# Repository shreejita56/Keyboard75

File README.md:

# Keyboard75

SO I made a custom 75 % layout Mechanical keyboard which has a rotor encoder at the top for brightness controlee as well . It is based on rp2040 chip  . SO I had to design the MCU circuit by myself as well . The PCB was designed on kicad and CAD was done on Fusion . firmware was written in VS-Code. It has a very compact design. The Keyboard also includes per switch LED and diodes to prevent ghosting. It connects to the PC via USB-C input .

## Features
 - Based on Rp2040 chip
 - had compact 75% keyboard layout
 - Per Switch LED and diode for ghosting prevention
 - USB-C Type for Connection
 - Uplifted CAD Design for comfortable typing

##  BOM

| Comment | Footprint | Quantity | Total Price ($) | Link |
|---|---|---:|---:|---|
| 33pF | 0603 | 4 | 0.0236 | https://jlcpcb.com/partdetail/2015-CL10C330JB8NNNC/C1663 |
| 0.1uF | 0603 | 10 | 0.124 | https://jlcpcb.com/partdetail/YAGEO-CC0603KRX7R9BB104/C14663 |
| 100nF | 0603 | 10 | 0.124 | https://jlcpcb.com/partdetail/YAGEO-CC0603KRX7R9BB104/C14663 |
| 10uF | 0603 | 4 | 0.1276 | https://jlcpcb.com/partdetail/20411-CL10A106KP8NNNC/C19702 |
| 1uF | 0603 | 4 | 0.0684 | https://jlcpcb.com/partdetail/16531-CL10A105KB8NNNC/C15849 |
| USB_C_Receptacle_USB2.0_16P | USB_C_Receptacle_G-Switch_GT-USB-7010ASV | 2 | 0.0988 | https://jlcpcb.com/partdetail/DEALON-USB_TYPE_C006/C2927026 |
| 5.1K | 0603 | 4 | 0.0076 | https://jlcpcb.com/partdetail/23913-0603WAF5101T5E/C23186 |
| 1K | 0603 | 4 | 0.0132 | https://jlcpcb.com/partdetail/21904-0603WAF1001T5E/C21190 |
| 27ohm | 0603 | 20 | 0.022 | https://jlcpcb.com/partdetail/23790019-RCA0327RJLF/C22356575 |
| 10K | 0603 | 4 | 0.0108 | https://jlcpcb.com/partdetail/26547-0603WAF1002T5E/C25804 |
| RP2040 | QFN-56-1EP_7x7mm_P0.4mm_EP3.2x3.2mm | 2 | 1.979 | https://jlcpcb.com/partdetail/RaspberryPi-RP2040/C2040 |
| 12MHz | Crystal_SMD_3225-4Pin_3.2x2.5mm | 5 | 2.14 | https://jlcpcb.com/partdetail/KDSDaishinku-DSX321G12MHz/C93234 |
| PCB + 3D Prints Cost | — | 1 | 30.80 | https://jlcpcb.com |
| PCBA Cost | — | 1 | 27.88 | https://jlcpcb.com |
| PCB Shipping | — | 1 | 14.03 | https://jlcpcb.com |
| Hot-swap | — | 90 | 6.75 | https://meckeys.com/shop/accessories/keyboard-accessories/key-switches/kailh-hot-swap-socket/?attribute_pa_variations=white |
| Mechanical Switch | — | 90 | 21.10 | https://meckeys.com/shop/accessories/keyboard-accessories/key-switches/akko-v3-pro-cream-black-switch/ |
| KEY-CAPS | — | 1 | 11.50 | https://meckeys.com/shop/accessories/keyboard-accessories/keycaps/side-engraved-keycap-set/?attribute_pa_pick-your-style=blackberry-side-printed |
| 0.1uF Capacitor | 0603 | 90 | 3.60 | https://sharvielectronics.com/product/0-1uf-16v-capacitor-0603-smd-package/ |
| 1N4007 Diodes | SOD-123FL | 90 | 2.60 | https://sharvielectronics.com/product/a7-1n4007-100v-1a-silicon-rectifier-diode-sod-123fl-smd-package/ |
| SK6812MINI-E | — | 90 | 8.10 | https://www.etstore.in/products/e9974?variant=48993209319675 |
| Components Shipping | — | 1 | 3.30 | https://www.etstore.in/ |
| **TOTAL** | — | — | **$132.67** | — |

### Schematic<br><br>

###  PCB Design<br><br>

### 3D Render <br><br>

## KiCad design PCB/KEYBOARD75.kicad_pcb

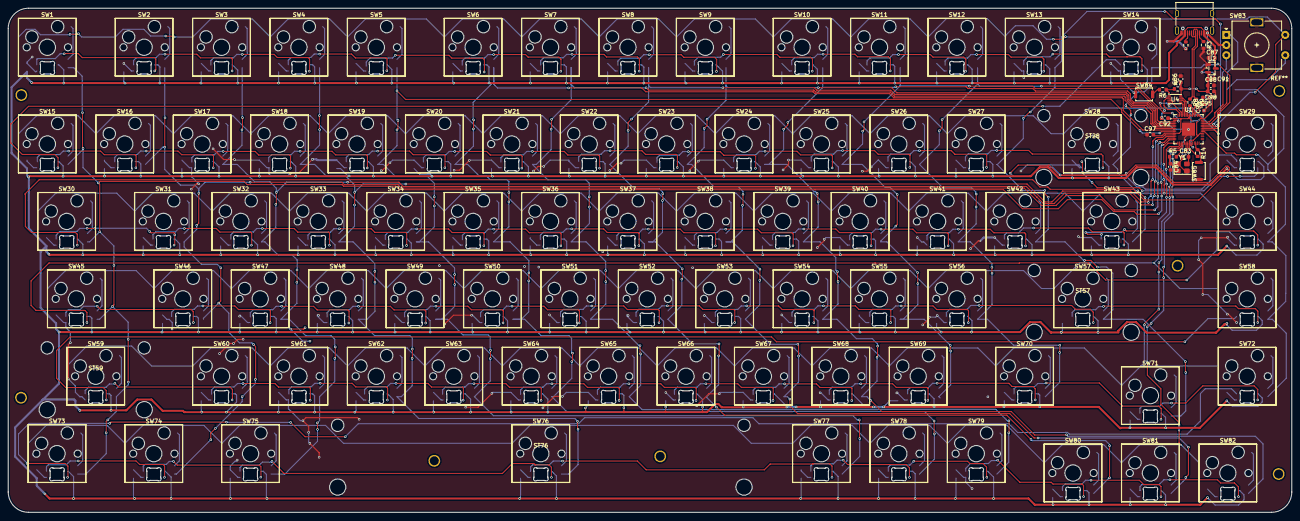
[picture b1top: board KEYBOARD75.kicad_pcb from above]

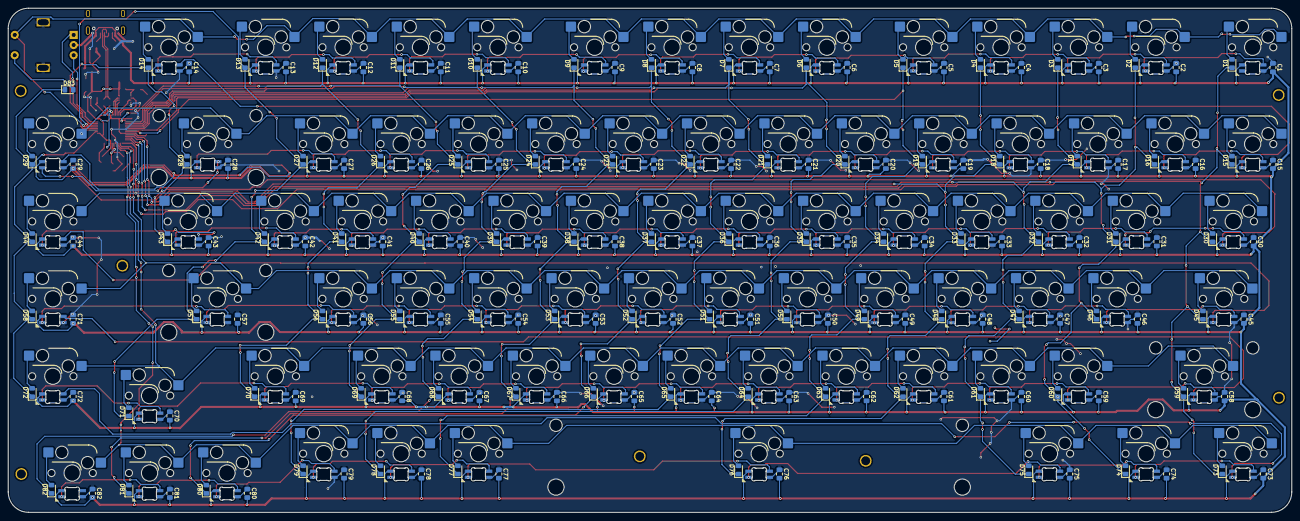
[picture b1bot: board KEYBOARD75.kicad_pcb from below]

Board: 2 copper layers, 315.9 x 124.1 mm, 360 parts (165 on the bottom side), 208 nets.

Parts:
C1, C2, C3, C4, C5, C6, C7, C8, C9, C10, C11, C12, C13, C14, C15, C16, C17, C18, C19, C20, C21, C22, C23, C24, C25, C26, C27, C28, C29, C30, C31, C32, C33, C34, C35, C36, C37, C38, C39, C40, C41, C42, C43, C44, C45, C46, C47, C48, C49, C50, C51, C52, C53, C54, C55, C56, C57, C58, C59, C60, C61, C62, C63, C64, C65, C66, C67, C68, C69, C70, C71, C72, C73, C74, C75, C76, C77, C78, C79, C80, C81, C82: 0.1 uf; C_0805_2012Metric_Pad1.18x1.45mm_HandSolder
C83, C84: 33pF; C_0603_1608Metric
C86, C88, C92: 0.1uF; C_0603_1608Metric
C87, C91: 10uF; C_0603_1608Metric
C94: 1uF; C_0603_1608Metric
C95, C97: 100 nf; C_0603_1608Metric
C98: 1uf; C_0603_1608Metric
D1, D2, D3, D4, D5, D6, D7, D8, D9, D10, D11, D12, D13, D14, D15, D16, D17, D18, D19, D20, D21, D22, D23, D24, D25, D26, D27, D28, D29, D30, D31, D32, D33, D34, D35, D36, D37, D38, D39, D40, D41, D42, D43, D44, D45, D46, D47, D48, D49, D50, D51, D52, D53, D54, D55, D56, D57, D58, D59, D60, D61, D62, D63, D64, D65, D66, D67, D68, D69, D70, D71, D72, D73, D74, D75, D76, D77, D78, D79, D80, D81, D82, D83: D; D_0805_2012Metric_Pad1.15x1.40mm_HandSolder
J1: USB_C_Receptacle_USB2.0_16P; USB_C_Receptacle_G-Switch_GT-USB-7010ASV
LED1: C; MX_SK6812MINI-E
LED2, LED3, LED4, LED5, LED6, LED7, LED8, LED9, LED10, LED11, LED12, LED13, LED14, LED15, LED16, LED17, LED18, LED19, LED20, LED21, LED22, LED23, LED24, LED25, LED26, LED27, LED28, LED29, LED30, LED31, LED32, LED33, LED34, LED35, LED36, LED37, LED38, LED39, LED40, LED41, LED42, LED43, LED44, LED45, LED46, LED47, LED48, LED49, LED50, LED51, LED52, LED53, LED54, LED55, LED56, LED57, LED58, LED59, LED60, LED61, LED62, LED63, LED64, LED65, LED66, LED67, LED68, LED69, LED70, LED71, LED72, LED73, LED74, LED75, LED76, LED77, LED78, LED79, LED80, LED81, LED82: MX_SK6812MINI-E
R3, R4: 5.1K; R_0603_1608Metric
R5, R6: 1K; R_0603_1608Metric
R7, R14: 10K; R_0603_1608Metric
R8, R9: 27 ohn; R_0603_1608Metric
ST28, ST57, ST59: MountingHole; Stabilizer_Cherry_MX_2.00u
ST76: MountingHole; Stabilizer_Cherry_MX_6.25u
SW1: ESC; SW_Hotswap_Kailh_MX_1.00u
SW2: F1; SW_Hotswap_Kailh_MX_1.00u
SW3: F2; SW_Hotswap_Kailh_MX_1.00u
SW4: F3; SW_Hotswap_Kailh_MX_1.00u
SW5: F4; SW_Hotswap_Kailh_MX_1.00u
SW6: F5; SW_Hotswap_Kailh_MX_1.00u
SW7: F6; SW_Hotswap_Kailh_MX_1.00u
SW8: F7; SW_Hotswap_Kailh_MX_1.00u
SW9: F8; SW_Hotswap_Kailh_MX_1.00u
SW10: F9; SW_Hotswap_Kailh_MX_1.00u
SW11: F10; SW_Hotswap_Kailh_MX_1.00u
SW12: F11; SW_Hotswap_Kailh_MX_1.00u
SW13: F12; SW_Hotswap_Kailh_MX_1.00u
SW14: Delete; SW_Hotswap_Kailh_MX_1.00u
SW15: `; SW_Hotswap_Kailh_MX_1.00u
SW16: 1; SW_Hotswap_Kailh_MX_1.00u
SW17: 2; SW_Hotswap_Kailh_MX_1.00u
SW18: 3; SW_Hotswap_Kailh_MX_1.00u
SW19: 4; SW_Hotswap_Kailh_MX_1.00u
SW20: 5; SW_Hotswap_Kailh_MX_1.00u
SW21: 6; SW_Hotswap_Kailh_MX_1.00u
SW22: 7; SW_Hotswap_Kailh_MX_1.00u
SW23: 8; SW_Hotswap_Kailh_MX_1.00u
SW24: 9; SW_Hotswap_Kailh_MX_1.00u
SW25: 0; SW_Hotswap_Kailh_MX_1.00u
SW26: -; SW_Hotswap_Kailh_MX_1.00u
SW27: +; SW_Hotswap_Kailh_MX_1.00u
SW28: Backspace; SW_Hotswap_Kailh_MX_1.00u
SW29: Home; SW_Hotswap_Kailh_MX_1.00u
SW30: Tab; SW_Hotswap_Kailh_MX_1.00u
SW31: Q; SW_Hotswap_Kailh_MX_1.00u
SW32: W; SW_Hotswap_Kailh_MX_1.00u
SW33: E; SW_Hotswap_Kailh_MX_1.00u
SW34: R; SW_Hotswap_Kailh_MX_1.00u
SW35: T; SW_Hotswap_Kailh_MX_1.00u
SW36: Y; SW_Hotswap_Kailh_MX_1.00u
SW37: U; SW_Hotswap_Kailh_MX_1.00u
SW38: I; SW_Hotswap_Kailh_MX_1.00u
SW39: O; SW_Hotswap_Kailh_MX_1.00u
SW40: P; SW_Hotswap_Kailh_MX_1.00u
SW41: [; SW_Hotswap_Kailh_MX_1.00u
SW42: ]; SW_Hotswap_Kailh_MX_1.00u
SW43: \; SW_Hotswap_Kailh_MX_1.00u
SW44: Pg Up; SW_Hotswap_Kailh_MX_1.00u
SW45: Caps Lock; SW_Hotswap_Kailh_MX_1.00u
SW46: A; SW_Hotswap_Kailh_MX_1.00u
SW47: S; SW_Hotswap_Kailh_MX_1.00u
SW48: D; SW_Hotswap_Kailh_MX_1.00u
SW49: F; SW_Hotswap_Kailh_MX_1.00u
SW50: G; SW_Hotswap_Kailh_MX_1.00u
SW51: H; SW_Hotswap_Kailh_MX_1.00u
SW52: J; SW_Hotswap_Kailh_MX_1.00u
SW53: K; SW_Hotswap_Kailh_MX_1.00u
SW54: L; SW_Hotswap_Kailh_MX_1.00u
SW55: ;; SW_Hotswap_Kailh_MX_1.00u
SW56: "; SW_Hotswap_Kailh_MX_1.00u
SW57: Enter; SW_Hotswap_Kailh_MX_1.00u
SW58: Pg Dn; SW_Hotswap_Kailh_MX_1.00u
SW59: L Shift; SW_Hotswap_Kailh_MX_1.00u
SW60: Z; SW_Hotswap_Kailh_MX_1.00u
SW61: X; SW_Hotswap_Kailh_MX_1.00u
SW62: C; SW_Hotswap_Kailh_MX_1.00u
SW63: V; SW_Hotswap_Kailh_MX_1.00u
SW64: B; SW_Hotswap_Kailh_MX_1.00u
SW65: N; SW_Hotswap_Kailh_MX_1.00u
SW66: M; SW_Hotswap_Kailh_MX_1.00u
SW67: ,; SW_Hotswap_Kailh_MX_1.00u
SW68: .; SW_Hotswap_Kailh_MX_1.00u
SW69: /; SW_Hotswap_Kailh_MX_1.00u
SW70: R Shift; SW_Hotswap_Kailh_MX_1.00u
SW71: Up Arrow; SW_Hotswap_Kailh_MX_1.00u
SW72: End; SW_Hotswap_Kailh_MX_1.00u
SW73: L Ctrl; SW_Hotswap_Kailh_MX_1.00u
SW74: Win; SW_Hotswap_Kailh_MX_1.00u
SW75, SW77: Alt; SW_Hotswap_Kailh_MX_1.00u
SW76: Space; SW_Hotswap_Kailh_MX_1.00u
SW78: Fn; SW_Hotswap_Kailh_MX_1.00u
SW79: R Ctrl; SW_Hotswap_Kailh_MX_1.00u
SW80: Left Arrow; SW_Hotswap_Kailh_MX_1.00u
SW81: Down Arrow; SW_Hotswap_Kailh_MX_1.00u
SW82: Right Arrow; SW_Hotswap_Kailh_MX_1.00u
SW83: RotaryEncoder_Switch_MP; RotaryEncoder_Alps_EC11E-Switch_Vertical_H20mm
SW84, SW85: SW_Push; SW_Push_SPST_NO_Alps_SKRK
U1: RP2040; QFN-56-1EP_7x7mm_P0.4mm_EP3.2x3.2mm
U2: MCP1700x-330xxTT; SOT-23
U4: W25Q16JVUXIQ TR; Winbond_USON-8-1EP_3x2mm_P0.5mm_EP0.2x1.6mm
Y1: 12 MHz; Crystal_SMD_3225-4Pin_3.2x2.5mm

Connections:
+3.3V: C86.1, C88.1, C91.1, C92.1, C97.2, C98.2, R7.2, R14.2, U1.1 (IOVDD), U1.10 (IOVDD), U1.22 (IOVDD), U1.33 (IOVDD), U1.42 (IOVDD), U1.43 (ADC_AVDD), U1.44 (VREG_IN), U1.48 (USB_VDD), U1.49 (IOVDD), U2.2 (VO), U4.8 (VCC)
+5V: C1.2, C2.2, C3.2, C4.2, C5.2, C6.2, C7.2, C8.2, C9.2, C10.2, C11.2, C12.2, C13.2, C14.2, C15.2, C16.2, C17.2, C18.2, C19.2, C20.2, C21.2, C22.2, C23.2, C24.2, C25.2, C26.2, C27.2, C28.2, C29.2, C30.2, C31.2, C32.2, C33.2, C34.2, C35.2, C36.2, C37.2, C38.2, C39.2, C40.2, C41.2, C42.2, C43.2, C44.2, C45.2, C46.2, C47.2, C48.2, C49.2, C50.2, C51.2, C52.2, C53.2, C54.2, C55.2, C56.2, C57.2, C58.2, C59.2, C60.2, C61.2, C62.2, C63.2, C64.2, C65.2, C66.2, C67.2, C68.2, C69.2, C70.2, C71.2, C72.2, C73.2, C74.2, C75.2, C76.2, C77.2, C78.2, C79.2, C80.2, C81.2, C82.2, C87.1, J1.A4 (VBUS), J1.A9 (VBUS), J1.B4 (VBUS), J1.B9 (VBUS), LED1.4 (VDD), LED2.4 (VDD), LED3.4 (VDD), LED4.4 (VDD), LED5.4 (VDD), LED6.4 (VDD), LED7.4 (VDD), LED8.4 (VDD), LED9.4 (VDD), LED10.4 (VDD), LED11.4 (VDD), LED12.4 (VDD), LED13.4 (VDD), LED14.4 (VDD), LED15.4 (VDD), LED16.4 (VDD), LED17.4 (VDD), LED18.4 (VDD), LED19.4 (VDD), LED20.4 (VDD), LED21.4 (VDD), LED22.4 (VDD), LED23.4 (VDD), LED24.4 (VDD), LED25.4 (VDD), LED26.4 (VDD), LED27.4 (VDD), LED28.4 (VDD), LED29.4 (VDD), LED30.4 (VDD), LED31.4 (VDD), LED32.4 (VDD), LED33.4 (VDD), LED34.4 (VDD), LED35.4 (VDD), LED36.4 (VDD), LED37.4 (VDD), LED38.4 (VDD), LED39.4 (VDD), LED40.4 (VDD), LED41.4 (VDD), LED42.4 (VDD), LED43.4 (VDD), LED44.4 (VDD), LED45.4 (VDD), LED46.4 (VDD), LED47.4 (VDD), LED48.4 (VDD), LED49.4 (VDD), LED50.4 (VDD), LED51.4 (VDD), LED52.4 (VDD), LED53.4 (VDD), LED54.4 (VDD), LED55.4 (VDD), LED56.4 (VDD), LED57.4 (VDD), LED58.4 (VDD), LED59.4 (VDD), LED60.4 (VDD), LED61.4 (VDD), LED62.4 (VDD), LED63.4 (VDD), LED64.4 (VDD), LED65.4 (VDD), LED66.4 (VDD), LED67.4 (VDD), LED68.4 (VDD), LED69.4 (VDD), LED70.4 (VDD), LED71.4 (VDD), LED72.4 (VDD), LED73.4 (VDD), LED74.4 (VDD), LED75.4 (VDD), LED76.4 (VDD), LED77.4 (VDD), LED78.4 (VDD), LED79.4 (VDD), LED80.4 (VDD), LED81.4 (VDD), LED82.4 (VDD), U2.3 (VI)
C1: D1.1 (K), D15.1 (K), D30.1 (K), D45.1 (K), D59.1 (K), D73.1 (K), U1.14 (GPIO11)
C2: D2.1 (K), D16.1 (K), D31.1 (K), D46.1 (K), D60.1 (K), D74.1 (K), U1.13 (GPIO10)
C3: D3.1 (K), D17.1 (K), D32.1 (K), D47.1 (K), D61.1 (K), D75.1 (K), U1.12 (GPIO9)
C4: D4.1 (K), D18.1 (K), D33.1 (K), D48.1 (K), D62.1 (K), D76.1 (K), U1.11 (GPIO8)
C5: D5.1 (K), D19.1 (K), D34.1 (K), D49.1 (K), D63.1 (K), D77.1 (K), U1.9 (GPIO7)
C6: D6.1 (K), D20.1 (K), D35.1 (K), D50.1 (K), D64.1 (K), D78.1 (K), U1.8 (GPIO6)
C7: D7.1 (K), D21.1 (K), D36.1 (K), D51.1 (K), D65.1 (K), D79.1 (K), U1.7 (GPIO5)
C8: D8.1 (K), D22.1 (K), D37.1 (K), D52.1 (K), D66.1 (K), D80.1 (K), U1.6 (GPIO4)
C9: D9.1 (K), D23.1 (K), D38.1 (K), D53.1 (K), D67.1 (K), D81.1 (K), U1.5 (GPIO3)
C10: D10.1 (K), D24.1 (K), D39.1 (K), D54.1 (K), D68.1 (K), D82.1 (K), U1.4 (GPIO2)
C11: D11.1 (K), D25.1 (K), D40.1 (K), D55.1 (K), D69.1 (K), U1.3 (GPIO1)
C12: D12.1 (K), D26.1 (K), D41.1 (K), D56.1 (K), D70.1 (K), U1.2 (GPIO0)
C13: D13.1 (K), D27.1 (K), D42.1 (K), D57.1 (K), D71.1 (K), U1.38 (GPIO26_ADC0)
C14: D14.1 (K), D28.1 (K), D43.1 (K), U1.36 (GPIO24)
C15: D29.1 (K), D44.1 (K), D58.1 (K), D72.1 (K), D83.1 (K), U1.34 (GPIO22)
E-A: SW83.A, U1.39 (GPIO27_ADC1)
E-B: SW83.B, U1.40 (GPIO28_ADC2)
E-SW1: D83.2 (A), SW83.S1
E-SW2: SW1.1, SW2.1, SW3.1, SW4.1, SW5.1, SW6.1, SW7.1, SW8.1, SW9.1, SW10.1, SW11.1, SW12.1, SW13.1, SW14.1, SW83.S2, U1.37 (GPIO25)
GND: C1.1, C2.1, C3.1, C4.1, C5.1, C6.1, C7.1, C8.1, C9.1, C10.1, C11.1, C12.1, C13.1, C14.1, C15.1, C16.1, C17.1, C18.1, C19.1, C20.1, C21.1, C22.1, C23.1, C24.1, C25.1, C26.1, C27.1, C28.1, C29.1, C30.1, C31.1, C32.1, C33.1, C34.1, C35.1, C36.1, C37.1, C38.1, C39.1, C40.1, C41.1, C42.1, C43.1, C44.1, C45.1, C46.1, C47.1, C48.1, C49.1, C50.1, C51.1, C52.1, C53.1, C54.1, C55.1, C56.1, C57.1, C58.1, C59.1, C60.1, C61.1, C62.1, C63.1, C64.1, C65.1, C66.1, C67.1, C68.1, C69.1, C70.1, C71.1, C72.1, C73.1, C74.1, C75.1, C76.1, C77.1, C78.1, C79.1, C80.1, C81.1, C82.1, C83.1, C84.1, C86.2, C87.2, C88.2, C91.2, C92.2, C94.1, C95.1, C97.1, C98.1, J1.A1 (GND), J1.A12 (GND), J1.B1 (GND), J1.B12 (GND), LED1.2 (VSS), LED2.2 (VSS), LED3.2 (VSS), LED4.2 (VSS), LED5.2 (VSS), LED6.2 (VSS), LED7.2 (VSS), LED8.2 (VSS), LED9.2 (VSS), LED10.2 (VSS), LED11.2 (VSS), LED12.2 (VSS), LED13.2 (VSS), LED14.2 (VSS), LED15.2 (VSS), LED16.2 (VSS), LED17.2 (VSS), LED18.2 (VSS), LED19.2 (VSS), LED20.2 (VSS), LED21.2 (VSS), LED22.2 (VSS), LED23.2 (VSS), LED24.2 (VSS), LED25.2 (VSS), LED26.2 (VSS), LED27.2 (VSS), LED28.2 (VSS), LED29.2 (VSS), LED30.2 (VSS), LED31.2 (VSS), LED32.2 (VSS), LED33.2 (VSS), LED34.2 (VSS), LED35.2 (VSS), LED36.2 (VSS), LED37.2 (VSS), LED38.2 (VSS), LED39.2 (VSS), LED40.2 (VSS), LED41.2 (VSS), LED42.2 (VSS), LED43.2 (VSS), LED44.2 (VSS), LED45.2 (VSS), LED46.2 (VSS), LED47.2 (VSS), LED48.2 (VSS), LED49.2 (VSS), LED50.2 (VSS), LED51.2 (VSS), LED52.2 (VSS), LED53.2 (VSS), LED54.2 (VSS), LED55.2 (VSS), LED56.2 (VSS), LED57.2 (VSS), LED58.2 (VSS), LED59.2 (VSS), LED60.2 (VSS), LED61.2 (VSS), LED62.2 (VSS), LED63.2 (VSS), LED64.2 (VSS), LED65.2 (VSS), LED66.2 (VSS), LED67.2 (VSS), LED68.2 (VSS), LED69.2 (VSS), LED70.2 (VSS), LED71.2 (VSS), LED72.2 (VSS), LED73.2 (VSS), LED74.2 (VSS), LED75.2 (VSS), LED76.2 (VSS), LED77.2 (VSS), LED78.2 (VSS), LED79.2 (VSS), LED80.2 (VSS), LED81.2 (VSS), LED82.2 (VSS), R3.2, R4.2, SW83.C, SW83.MP, SW84.1, SW85.1, U1.19 (TESTEN), U1.57 (GND), U2.1 (GND), U4.4 (GND), Y1.2, Y1.4
unnamed: C84.2, R5.1, Y1.1
unnamed: D1.2 (A), SW1.2
unnamed: D2.2 (A), SW2.2
unnamed: D3.2 (A), SW3.2
unnamed: D4.2 (A), SW4.2
unnamed: D5.2 (A), SW5.2
unnamed: D6.2 (A), SW6.2
unnamed: D7.2 (A), SW7.2
unnamed: D8.2 (A), SW8.2
unnamed: D9.2 (A), SW9.2
unnamed: D10.2 (A), SW10.2
unnamed: D11.2 (A), SW11.2
unnamed: D12.2 (A), SW12.2
unnamed: D13.2 (A), SW13.2
unnamed: D14.2 (A), SW14.2
unnamed: D15.2 (A), SW15.2
unnamed: D16.2 (A), SW16.2
unnamed: D17.2 (A), SW17.2
unnamed: D18.2 (A), SW18.2
unnamed: D19.2 (A), SW19.2
unnamed: D20.2 (A), SW20.2
unnamed: D21.2 (A), SW21.2
unnamed: D22.2 (A), SW22.2
unnamed: D23.2 (A), SW23.2
unnamed: D24.2 (A), SW24.2
unnamed: D25.2 (A), SW25.2
unnamed: D26.2 (A), SW26.2
unnamed: D27.2 (A), SW27.2
unnamed: D28.2 (A), SW28.2
unnamed: D29.2 (A), SW29.2
unnamed: D30.2 (A), SW30.2
unnamed: D31.2 (A), SW31.2
unnamed: D32.2 (A), SW32.2
unnamed: D33.2 (A), SW33.2
unnamed: D34.2 (A), SW34.2
unnamed: D35.2 (A), SW35.2
unnamed: D36.2 (A), SW36.2
unnamed: D37.2 (A), SW37.2
unnamed: D38.2 (A), SW38.2
unnamed: D39.2 (A), SW39.2
unnamed: D40.2 (A), SW40.2
unnamed: D41.2 (A), SW41.2
unnamed: D42.2 (A), SW42.2
unnamed: D43.2 (A), SW43.2
unnamed: D44.2 (A), SW44.2
unnamed: D45.2 (A), SW45.2
unnamed: D46.2 (A), SW46.2
unnamed: D47.2 (A), SW47.2
unnamed: D48.2 (A), SW48.2
unnamed: D49.2 (A), SW49.2
unnamed: D50.2 (A), SW50.2
unnamed: D51.2 (A), SW51.2
unnamed: D52.2 (A), SW52.2
unnamed: D53.2 (A), SW53.2
unnamed: D54.2 (A), SW54.2
unnamed: D55.2 (A), SW55.2
unnamed: D56.2 (A), SW56.2
unnamed: D57.2 (A), SW57.2
unnamed: D58.2 (A), SW58.2
unnamed: D59.2 (A), SW59.2
unnamed: D60.2 (A), SW60.2
unnamed: D61.2 (A), SW61.2
unnamed: D62.2 (A), SW62.2
unnamed: D63.2 (A), SW63.2
unnamed: D64.2 (A), SW64.2
unnamed: D65.2 (A), SW65.2
unnamed: D66.2 (A), SW66.2
unnamed: D67.2 (A), SW67.2
unnamed: D68.2 (A), SW68.2
unnamed: D69.2 (A), SW69.2
unnamed: D70.2 (A), SW70.2
unnamed: D71.2 (A), SW71.2
unnamed: D72.2 (A), SW72.2
unnamed: D73.2 (A), SW73.2
unnamed: D74.2 (A), SW74.2
unnamed: D75.2 (A), SW75.2
unnamed: D76.2 (A), SW76.2
unnamed: D77.2 (A), SW77.2
unnamed: D78.2 (A), SW78.2
unnamed: D79.2 (A), SW79.2
unnamed: D80.2 (A), SW80.2
unnamed: D81.2 (A), SW81.2
unnamed: D82.2 (A), SW82.2
unnamed: J1.A5 (CC1), R3.1
unnamed: J1.B5 (CC2), R4.1
unnamed: LED1.1 (DOUT), LED2.3 (DIN)
unnamed: LED2.1 (DOUT), LED3.3 (DIN)
unnamed: LED3.1 (DOUT), LED4.3 (DIN)
unnamed: LED4.1 (DOUT), LED5.3 (DIN)
unnamed: LED5.1 (DOUT), LED6.3 (DIN)
unnamed: LED6.1 (DOUT), LED7.3 (DIN)
unnamed: LED7.1 (DOUT), LED8.3 (DIN)
unnamed: LED8.1 (DOUT), LED9.3 (DIN)
unnamed: LED9.1 (DOUT), LED10.3 (DIN)
unnamed: LED10.1 (DOUT), LED11.3 (DIN)
unnamed: LED11.1 (DOUT), LED12.3 (DIN)
unnamed: LED12.1 (DOUT), LED13.3 (DIN)
unnamed: LED13.1 (DOUT), LED14.3 (DIN)
unnamed: LED14.1 (DOUT), LED15.3 (DIN)
unnamed: LED15.1 (DOUT), LED16.3 (DIN)
unnamed: LED16.1 (DOUT), LED17.3 (DIN)
unnamed: LED17.1 (DOUT), LED18.3 (DIN)
unnamed: LED18.1 (DOUT), LED19.3 (DIN)
unnamed: LED19.1 (DOUT), LED20.3 (DIN)
unnamed: LED20.1 (DOUT), LED21.3 (DIN)
unnamed: LED21.1 (DOUT), LED22.3 (DIN)
unnamed: LED22.1 (DOUT), LED23.3 (DIN)
unnamed: LED23.1 (DOUT), LED24.3 (DIN)
unnamed: LED24.1 (DOUT), LED25.3 (DIN)
unnamed: LED25.1 (DOUT), LED26.3 (DIN)
unnamed: LED26.1 (DOUT), LED27.3 (DIN)
unnamed: LED27.1 (DOUT), LED28.3 (DIN)
unnamed: LED28.1 (DOUT), LED29.3 (DIN)
unnamed: LED29.1 (DOUT), LED30.3 (DIN)
unnamed: LED30.1 (DOUT), LED31.3 (DIN)
unnamed: LED31.1 (DOUT), LED32.3 (DIN)
unnamed: LED32.1 (DOUT), LED33.3 (DIN)
unnamed: LED33.1 (DOUT), LED34.3 (DIN)
unnamed: LED34.1 (DOUT), LED35.3 (DIN)
unnamed: LED35.1 (DOUT), LED36.3 (DIN)
unnamed: LED36.1 (DOUT), LED37.3 (DIN)
unnamed: LED37.1 (DOUT), LED38.3 (DIN)
unnamed: LED38.1 (DOUT), LED39.3 (DIN)
unnamed: LED39.1 (DOUT), LED40.3 (DIN)
unnamed: LED40.1 (DOUT), LED41.3 (DIN)
unnamed: LED41.1 (DOUT), LED42.3 (DIN)
unnamed: LED42.1 (DOUT), LED43.3 (DIN)
unnamed: LED43.1 (DOUT), LED44.3 (DIN)
unnamed: LED44.1 (DOUT), LED45.3 (DIN)
unnamed: LED45.1 (DOUT), LED46.3 (DIN)
unnamed: LED46.1 (DOUT), LED47.3 (DIN)
unnamed: LED47.1 (DOUT), LED48.3 (DIN)
unnamed: LED48.1 (DOUT), LED49.3 (DIN)
unnamed: LED49.1 (DOUT), LED50.3 (DIN)
unnamed: LED50.1 (DOUT), LED51.3 (DIN)
unnamed: LED51.1 (DOUT), LED52.3 (DIN)
unnamed: LED52.1 (DOUT), LED53.3 (DIN)
unnamed: LED53.1 (DOUT), LED54.3 (DIN)
unnamed: LED54.1 (DOUT), LED55.3 (DIN)
unnamed: LED55.1 (DOUT), LED56.3 (DIN)
unnamed: LED56.1 (DOUT), LED57.3 (DIN)
unnamed: LED57.1 (DOUT), LED58.3 (DIN)
unnamed: LED58.1 (DOUT), LED59.3 (DIN)
unnamed: LED59.1 (DOUT), LED60.3 (DIN)
unnamed: LED60.1 (DOUT), LED61.3 (DIN)
unnamed: LED61.1 (DOUT), LED62.3 (DIN)
unnamed: LED62.1 (DOUT), LED63.3 (DIN)
unnamed: LED63.1 (DOUT), LED64.3 (DIN)
unnamed: LED64.1 (DOUT), LED65.3 (DIN)
unnamed: LED65.1 (DOUT), LED66.3 (DIN)
unnamed: LED66.1 (DOUT), LED67.3 (DIN)
unnamed: LED67.1 (DOUT), LED68.3 (DIN)
unnamed: LED68.1 (DOUT), LED69.3 (DIN)
unnamed: LED69.1 (DOUT), LED70.3 (DIN)
unnamed: LED70.1 (DOUT), LED71.3 (DIN)
unnamed: LED71.1 (DOUT), LED72.3 (DIN)
unnamed: LED72.1 (DOUT), LED73.3 (DIN)
unnamed: LED73.1 (DOUT), LED74.3 (DIN)
unnamed: LED74.1 (DOUT), LED75.3 (DIN)
unnamed: LED75.1 (DOUT), LED76.3 (DIN)
unnamed: LED76.1 (DOUT), LED77.3 (DIN)
unnamed: LED77.1 (DOUT), LED78.3 (DIN)
unnamed: LED78.1 (DOUT), LED79.3 (DIN)
unnamed: LED79.1 (DOUT), LED80.3 (DIN)
unnamed: LED80.1 (DOUT), LED81.3 (DIN)
unnamed: LED81.1 (DOUT), LED82.3 (DIN)
unnamed: R6.2, SW84.2
unnamed: R14.1, SW85.2, U1.26 (RUN)
unnamed: R9.2, U1.46 (USB_DM)
unnamed: R8.2, U1.47 (USB_DP)
unnamed: C94.2, C95.2, U1.23 (DVDD), U1.45 (VREG_VOUT), U1.50 (DVDD)
QSPI_SCLK: U1.52 (QSPI_SCLK), U4.6 (CLK)
QSPI_SD0: U1.53 (QSPI_SD0), U4.5 (DI/IO_{0})
QSPI_SD1: U1.55 (QSPI_SD1), U4.2 (DO/IO_{1})
QSPI_SD2: U1.54 (QSPI_SD2), U4.3 (~WP/IO_{2})
QSPI_SD3: U1.51 (QSPI_SD3), U4.7 (~HOLD/~RESET/IO_{3})
QSPI_SS: R6.1, R7.1, U4.1 (~CS)
R2: SW15.1, SW16.1, SW17.1, SW18.1, SW19.1, SW20.1, SW21.1, SW22.1, SW23.1, SW24.1, SW25.1, SW26.1, SW27.1, SW28.1, SW29.1, U1.35 (GPIO23)
R3: SW30.1, SW31.1, SW32.1, SW33.1, SW34.1, SW35.1, SW36.1, SW37.1, SW38.1, SW39.1, SW40.1, SW41.1, SW42.1, SW43.1, SW44.1, U1.15 (GPIO12)
R4: SW45.1, SW46.1, SW47.1, SW48.1, SW49.1, SW50.1, SW51.1, SW52.1, SW53.1, SW54.1, SW55.1, SW56.1, SW57.1, SW58.1, U1.16 (GPIO13)
R5: SW59.1, SW60.1, SW61.1, SW62.1, SW63.1, SW64.1, SW65.1, SW66.1, SW67.1, SW68.1, SW69.1, SW70.1, SW71.1, SW72.1, U1.17 (GPIO14)
R6: SW73.1, SW74.1, SW75.1, SW76.1, SW77.1, SW78.1, SW79.1, SW80.1, SW81.1, SW82.1, U1.18 (GPIO15)
XIN: C83.2, U1.20 (XIN), Y1.3
XOUT: R5.2, U1.21 (XOUT)
_D+: J1.A6 (D+), J1.B6 (D+), R8.1
_D-: J1.A7 (D-), J1.B7 (D-), R9.1
